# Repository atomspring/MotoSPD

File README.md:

# MotoSPD
ESP32-based Motorcycle speedometer

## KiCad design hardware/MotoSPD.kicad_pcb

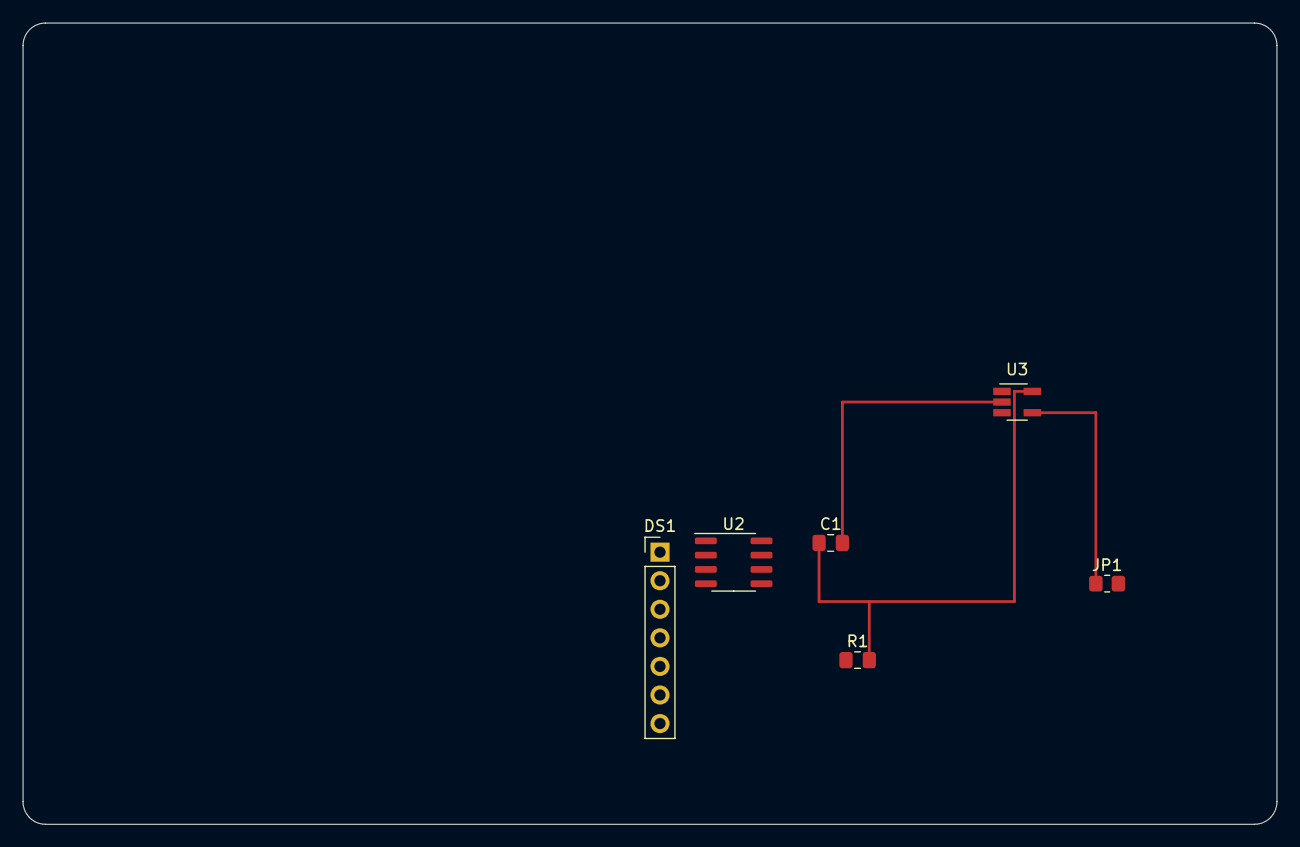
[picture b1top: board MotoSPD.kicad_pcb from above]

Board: 2 copper layers, 111.5 x 71.2 mm, 6 parts (0 on the bottom side), 3 nets.

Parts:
C1: 10uF; C_0805_2012Metric_Pad1.18x1.45mm_HandSolder
DS1: SSD1309; PinHeader_1x07_P2.54mm_Vertical
JP1: Jumper_2_Bridged; R_0805_2012Metric_Pad1.20x1.40mm_HandSolder
R1: 16R; C_0805_2012Metric_Pad1.18x1.45mm_HandSolder
U2: MAX33011EASA+; SOIC-8_3.9x4.9mm_P1.27mm
U3: TPS2400; SOT-23-5_HandSoldering

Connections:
GND: C1.2, U3.2 (GND)
unnamed: JP1.1 (A), U3.4 (Gate)
unnamed: C1.1, R1.2, U3.5 (VIN)

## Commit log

2024-11-21 Update LICENSE
2024-11-21 Update LICENSE
    succinct-ified
2024-11-21 Start GIT tracking..
2024-11-21 Refactored project layout
2024-11-21 Cleanup hardware layout
2024-11-21 Making progress, rm\'d extraneous files, added library
